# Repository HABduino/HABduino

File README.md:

## Habduino

This is the original code base for Habduino V4.X boards. It is still suitable for flights but is no longer maintained or supported. Hardware definitions are all current. 

This code provides simultaneous (where legal and supported by the hardware installed) transmission of radio telemetry via RTTY and APRS on Habduino Arduino addon boards for High Altitude Ballooning. 

## Move to Flextrack

We strongly recommend you move to Dave Akermans Flextrack as this is updated and maintained. We have forked the Flextrack code here https://github.com/HABduino/FlexTrack and made Habduino specific amendments.

## Disclaimer

The Habduino code is provided as is with no guarantees of performance or operation. 

If you decide to use this code under a balloon it’s your responsibility to ensure you comply with the local legislation and laws regarding meteorological balloon launching and radio transmission in the air. 
The Radiometrix NTX2B 434Mhz is NOT license exempt in the United States of America and does need a radio amateur license.

Use of APRS requires a radio amateur license in all countries and a number of countries don’t permit the airborne use of APRS under any circumstances. 

It is YOUR responsibility to ensure Habduino hardware and code is used safely and legally please review the safety section on the website. 

## Further Reading on High Altitude Ballooning

Please read this http://www.daveakerman.com/?p=1732

## License

The hardware design & code for Habduino is released under a Creative Commons License 3.0 Attribution-ShareAlike License : http://creativecommons.org/licenses/by-sa/3.0/

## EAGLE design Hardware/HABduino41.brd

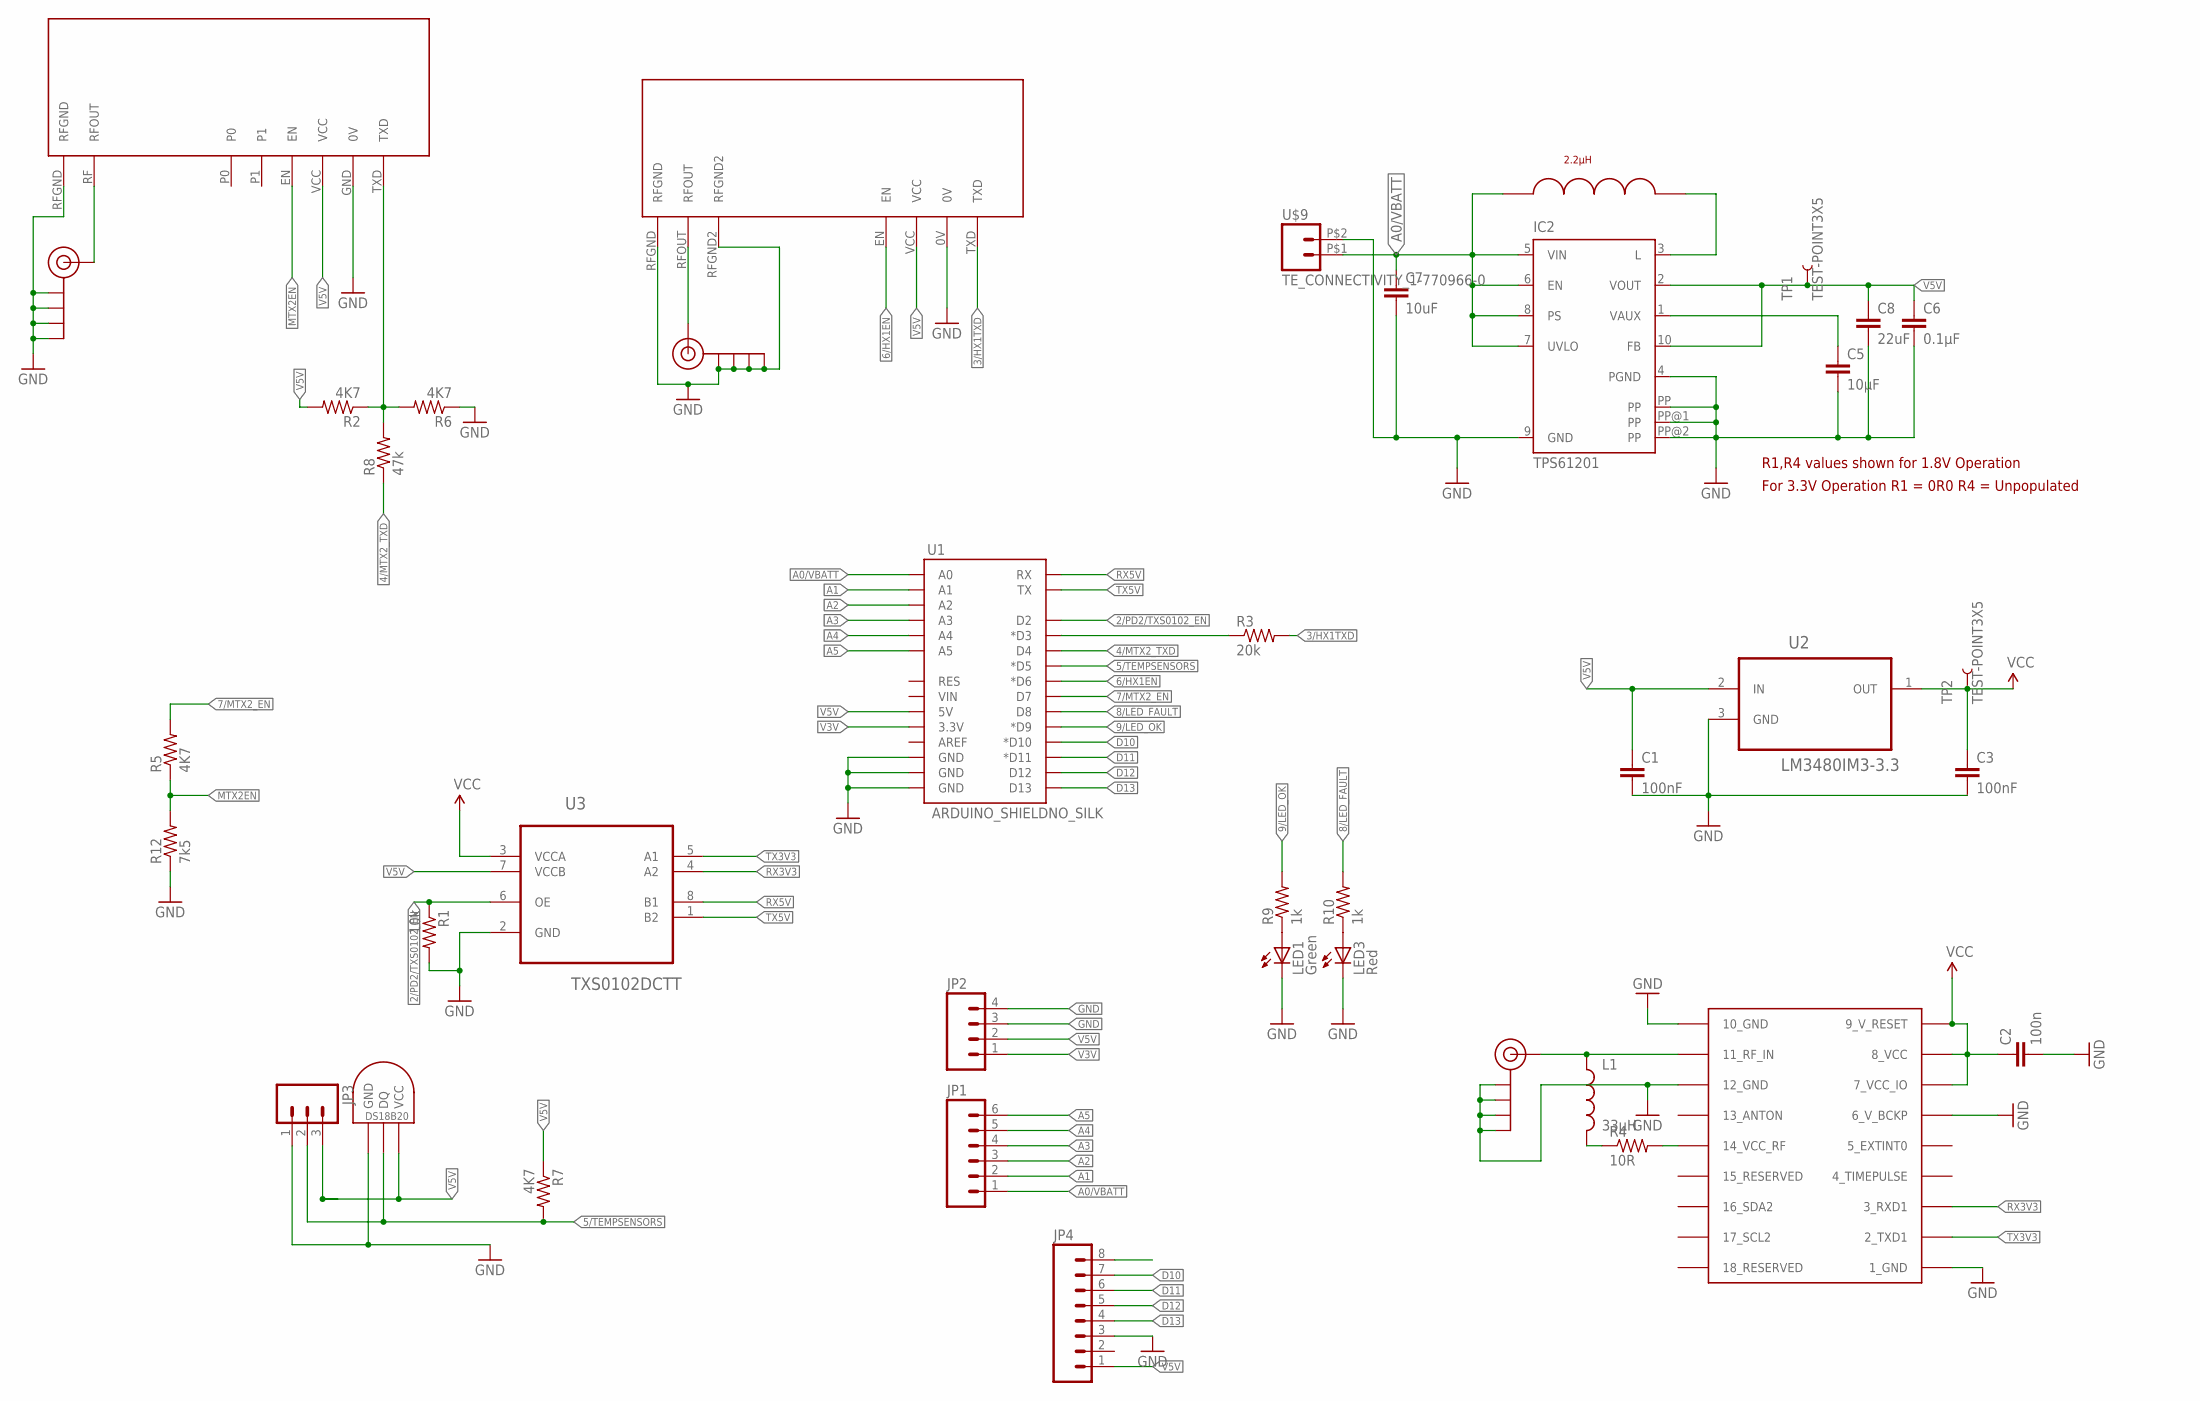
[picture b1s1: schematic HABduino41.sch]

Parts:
C1, C3: 100nF; 0603-CAP
C2: 100n; 0603-CAP
C5: 10µF; 0603-CAP
C6: 0.1µF; 0603-CAP
C7: 10uF; 1206
C8: 22uF; 1206
IC2: TPS61201; S-PDSO-N10
J$1, J$2, J$4: SMA_EDGE; SMA-EDGE
JP1: M06SIP; 1X06
JP2: M04PTH; 1X04
JP3: M03PTH; 1X03
JP4: M081X08; 1X08
L1: 33µH; 0603
LED1: Green; LED-0603
LED3: Red; LED-0603
LPS4018: 2.2µH; COILCRAFT_LPS4018
R1: 10k; 0603-RES
R2, R5, R6, R7: 4K7; 0603-RES
R3: 20k; 0603-RES
R4: 10R; 0603-RES
R8: 47k; 0603-RES
R9, R10: 1k; 0603-RES
R12: 7k5; 0603-RES
TEMP: DS1821; DS18B20_SOIC
TP1, TP2: TEST-POINT3X5; PAD.03X.05
U1: ARDUINO_SHIELDNO_SILK; DUEMILANOVE_VIAS
U2: LM3480IM3-3.3; SOT95P251X112-3N
U3: TXS0102DCTT; SOP65P400X130-8N
U$1: UBLOX_MAX
U$2: RADIOMETRIX-HX1
U$4: RADIOMETRIX-MTX2
U$9: TE_CONNECTIVITY_1-770966-0; FARNELL 1098556

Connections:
2/PD2/TXS0102_EN: R1.1, U1.D2, U3.6 (OE)
3/HX1TXD: R3.2, U$2.TXD
4/MTX2_TXD: R8.1, U1.D4
5/TEMPSENSORS: JP3.2, R7.2, TEMP.DQ, U1.D5 (*D5)
6/HX1EN: U1.D6 (*D6), U$2.EN
7/MTX2_EN: R5.2, U1.D7
8/LED_FAULT: R10.2, U1.D8
9/LED_OK: R9.2, U1.D9 (*D9)
A0/VBATT: C7.1, IC2.5 (VIN), IC2.6 (EN), IC2.7 (UVLO), IC2.8 (PS), JP1.1, LPS4018.P$1, U1.A0, U$9.P$1 (1)
A1: JP1.2, JP4.8, U1.A1
A2: JP1.3, U1.A2
A3: JP1.4, U1.A3
A4: JP1.5, U1.A4
A5: JP1.6, U1.A5
D10: JP4.7, U1.D10 (*D10)
D11: JP4.6, U1.D11 (*D11)
D12: JP4.5, U1.D12
D13: JP4.4, U1.D13
GND: C1.2, C2.2, C3.2, C5.2, C6.2, C7.2, C8.2, IC2.4 (PGND), IC2.9 (GND), IC2.PP, IC2.PP@1 (PP), IC2.PP@2 (PP), J$1.GND@0 (GND), J$1.GND@1 (GND), J$1.GND@2 (GND), J$1.GND@3 (GND), J$2.GND@0 (GND), J$2.GND@1 (GND), J$2.GND@2 (GND), J$2.GND@3 (GND), J$4.GND@0 (GND), J$4.GND@1 (GND), J$4.GND@2 (GND), J$4.GND@3 (GND), JP2.3, JP2.4, JP3.1, JP4.3, LED1.C, LED3.C, R1.2, R6.1, R12.1, TEMP.GND, U1.GND@0 (GND), U1.GND@1 (GND), U1.GND@2 (GND), U2.3 (GND), U3.2 (GND), U$1.1_GND, U$1.6_V_BCKP, U$1.10_GND, U$1.12_GND, U$2.0V, U$2.RFGND, U$2.RFGND2, U$4.GND (0V), U$4.RFGND, U$9.P$2 (2)
MTX2EN: R5.1, R12.2, U$4.EN
unnamed: R3.1, U1.D3 (*D3)
unnamed: J$1.SIG (SIGNAL), U$4.RF (RFOUT)
unnamed: J$2.SIG (SIGNAL), L1.1, U$1.11_RF_IN
unnamed: IC2.3 (L), LPS4018.P$2
unnamed: J$4.SIG (SIGNAL), U$2.RFOUT
unnamed: R2.1, R6.2, R8.2, U$4.TXD
unnamed: C5.1, IC2.1 (VAUX)
unnamed: LED1.A, R9.1
unnamed: LED3.A, R10.1
unnamed: L1.2, R4.1
unnamed: R4.2, U$1.14_VCC_RF
RX3V3: U3.4 (A2), U$1.3_RXD1
RX5V: U1.RX, U3.8 (B1)
TX3V3: U3.5 (A1), U$1.2_TXD1
TX5V: U1.TX, U3.1 (B2)
V3V: JP2.1, U1.3.3V
V5V: C1.1, C6.1, C8.1, IC2.2 (VOUT), IC2.10 (FB), JP2.2, JP3.3, JP4.1, R2.2, R7.1, TEMP.VCC, TP1.P$1, U1.5V, U2.2 (IN), U3.7 (VCCB), U$2.VCC, U$4.VCC
VCC: C2.1, C3.1, TP2.P$1, U2.1 (OUT), U3.3 (VCCA), U$1.7_VCC_IO, U$1.8_VCC, U$1.9_V_RESET

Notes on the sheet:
R1,R4 values shown for 1.8V Operation
For 3.3V Operation R1 = 0R0 R4 = Unpopulated

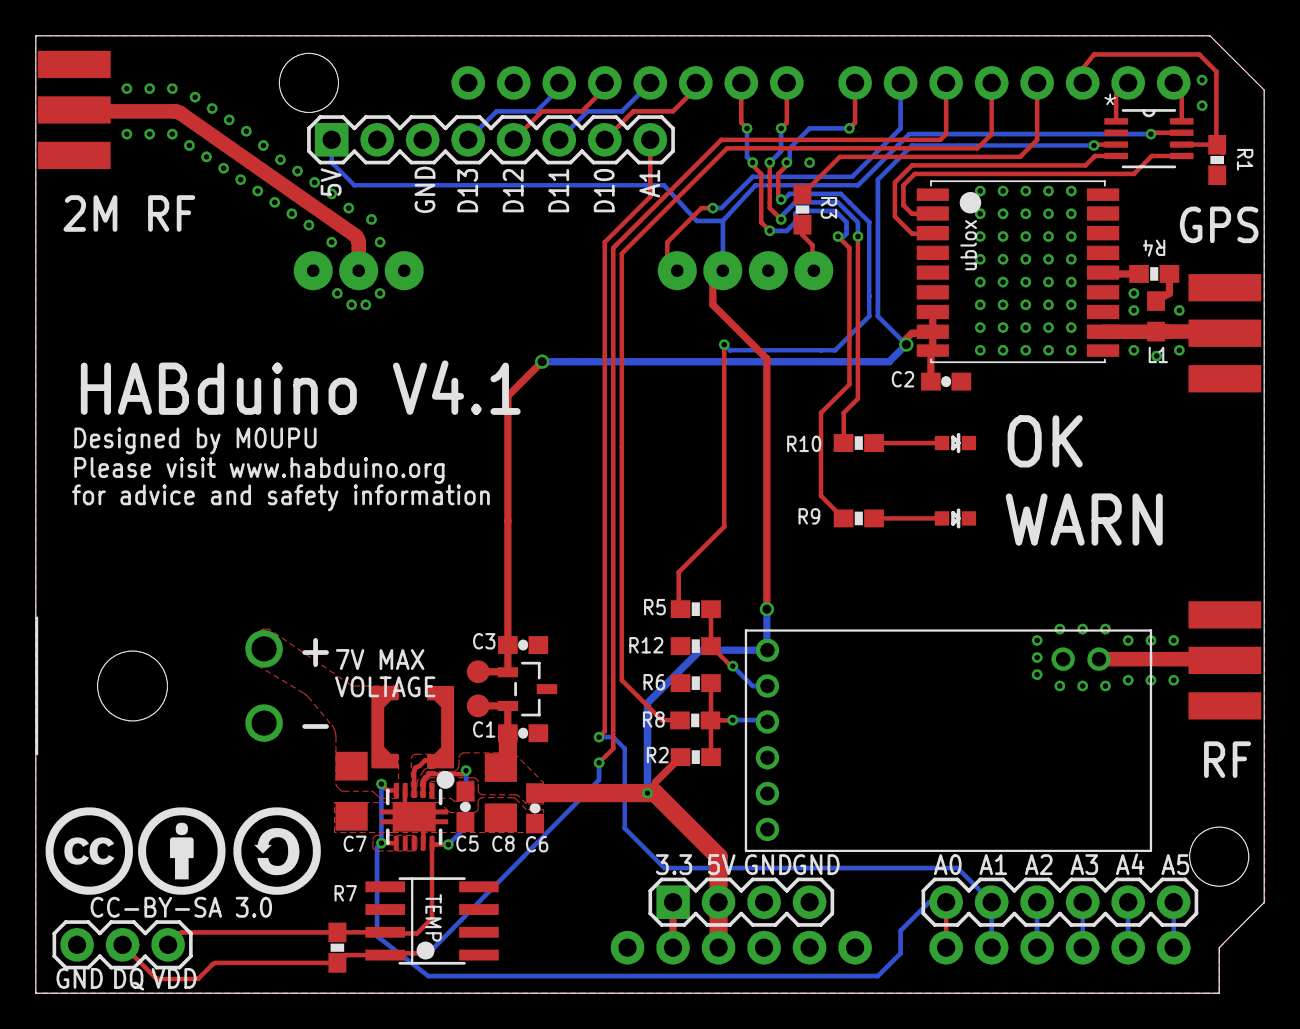
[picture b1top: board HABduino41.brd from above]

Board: 2 copper layers, 68.5 x 53.4 mm, 43 parts (1 on the bottom side), 38 nets.

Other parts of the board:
U$3: CC
U$5: CC-BY-21
U$6: CC-SA-21

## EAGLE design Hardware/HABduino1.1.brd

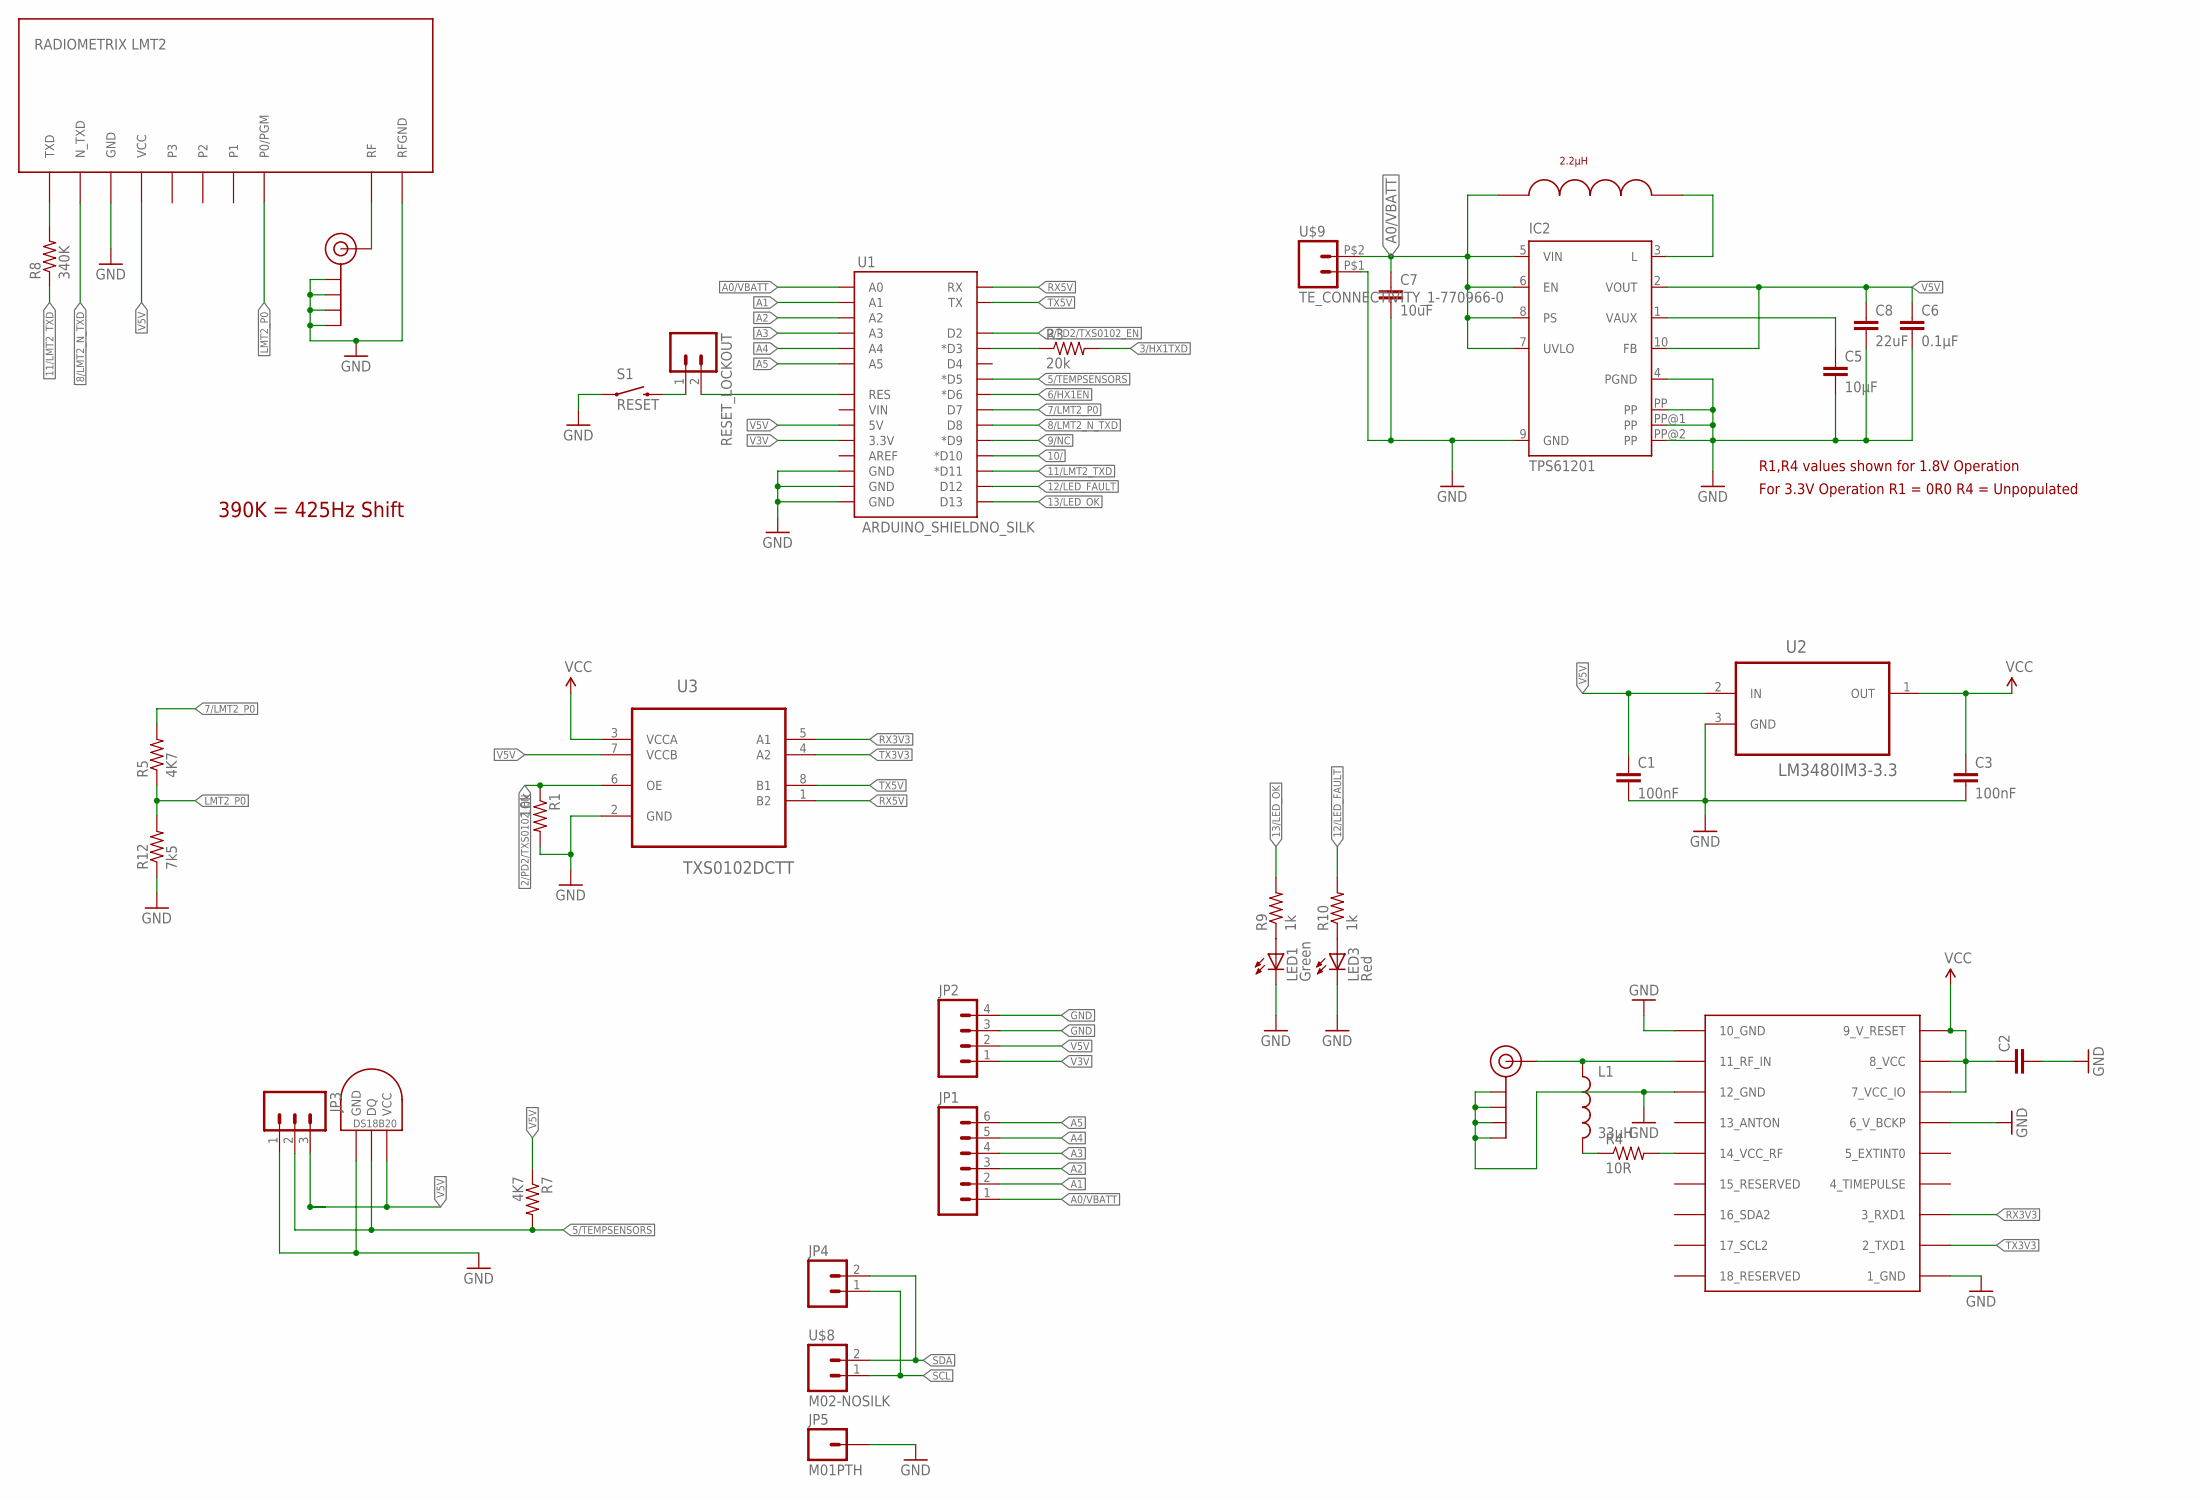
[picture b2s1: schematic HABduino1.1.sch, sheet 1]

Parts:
C1, C3: 100nF; 0603-CAP
C2: CAP0603-CAP; 0603-CAP
C5: 10µF; 0603-CAP
C6: 0.1µF; 0603-CAP
C7: 10uF; 1206
C8: 22uF; 1206
IC2: TPS61201; S-PDSO-N10
J$1, J$2: SMA_EDGE; SMA-EDGE
JP1: M06SIP; 1X06
JP2: M04PTH; 1X04
JP3: M03PTH; 1X03
JP4: M02PTH; 1X02
JP5: M01PTH; 1X01
L1: 33µH; 0603
LED1: Green; LED-0603
LED3: Red; LED-0603
R1: 10k; 0603-RES
R3: 20k; 0603-RES
R4: 10R; 0603-RES
R5, R7: 4K7; 0603-RES
R8: 340K; 0603-RES
R9, R10: 1k; 0603-RES
R12: 7k5; 0603-RES
RESET_LOCKOUT: M02PTH; 1X02
S1: RESET; TACTILE_SWITCH_TALL
TEMPINT: DS1821; DS1820
U1: ARDUINO_SHIELDNO_SILK; DUEMILANOVE_VIAS
U2: LM3480IM3-3.3; SOT95P251X112-3N
U3: TXS0102DCTT; SOP65P400X130-8N
U$1: UBLOX_MAX-6
U$2: RADIOMETRIX_LMT2; RADIOMETRIX-LMT2
U$8: M02-NOSILK
U$9: TE_CONNECTIVITY_1-770966-0; FARNELL 1098556
U$10: 2.2µH; COILCRAFT_LPS4018

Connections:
2/PD2/TXS0102_EN: R1.1, U1.D2, U3.6 (OE)
3/HX1TXD: R3.2; also elsewhere on the board
5/TEMPSENSORS: JP3.2, R7.2, TEMPINT.DQ, U1.D5 (*D5)
6/HX1EN: U1.D6 (*D6); also elsewhere on the board
7/LMT2_P0: R5.2, U1.D7
8/LMT2_N_TXD: U1.D8, U$2.N_TXE (N_TXD)
9/NC: U1.D9 (*D9)
10/: U1.D10 (*D10)
11/LMT2_TXD: R8.1, U1.D11 (*D11)
12/LED_FAULT: R10.2, U1.D12
13/LED_OK: R9.2, U1.D13
A0/VBATT: C7.1, IC2.5 (VIN), IC2.6 (EN), IC2.7 (UVLO), IC2.8 (PS), JP1.1, U1.A0, U$9.P$2 (2), U$10.P$1
A1: JP1.2, U1.A1
A2: JP1.3, U1.A2
A3: JP1.4, U1.A3
A4: JP1.5, U1.A4
A5: JP1.6, U1.A5
GND: C1.2, C2.2, C3.2, C5.2, C6.2, C7.2, C8.2, IC2.4 (PGND), IC2.9 (GND), IC2.PP, IC2.PP@1 (PP), IC2.PP@2 (PP), J$1.GND@0 (GND), J$1.GND@1 (GND), J$1.GND@2 (GND), J$1.GND@3 (GND), J$2.GND@0 (GND), J$2.GND@1 (GND), J$2.GND@2 (GND), J$2.GND@3 (GND), JP2.3, JP2.4, JP3.1, JP5.1, LED1.C, LED3.C, R1.2, R12.1, S1.A2 (1), TEMPINT.GND, U1.GND@0 (GND), U1.GND@1 (GND), U1.GND@2 (GND), U2.3 (GND), U3.2 (GND), U$1.1_GND, U$1.6_V_BCKP, U$1.10_GND, U$1.12_GND, U$2.GND, U$2.RFGND, U$9.P$1 (1); also elsewhere on the board
LMT2_P0: R5.1, R12.2, U$2.P0/PGM
unnamed: R3.1, U1.D3 (*D3)
unnamed: J$1.SIG (SIGNAL), U$2.RF
unnamed: J$2.SIG (SIGNAL), L1.1, U$1.11_RF_IN
unnamed: IC2.3 (L), U$10.P$2
unnamed: RESET_LOCKOUT.1, S1.B2 (2)
unnamed: RESET_LOCKOUT.2, U1.RES
unnamed: C5.1, IC2.1 (VAUX)
unnamed: LED1.A, R9.1
unnamed: LED3.A, R10.1
unnamed: L1.2, R4.1
unnamed: R4.2, U$1.14_VCC_RF
RX3V3: U3.5 (A1), U$1.3_RXD1
RX5V: U1.RX, U3.1 (B2)
SCL: JP4.1, U$8.1
SDA: JP4.2, U$8.2
TX3V3: U3.4 (A2), U$1.2_TXD1
TX5V: U1.TX, U3.8 (B1)
V3V: JP2.1, U1.3.3V
V5V: C1.1, C6.1, C8.1, IC2.2 (VOUT), IC2.10 (FB), JP2.2, JP3.3, R7.1, TEMPINT.VDD (VCC), U1.5V, U2.2 (IN), U3.7 (VCCB), U$2.VCC; also elsewhere on the board
VCC: C2.1, C3.1, U2.1 (OUT), U3.3 (VCCA), U$1.7_VCC_IO, U$1.8_VCC, U$1.9_V_RESET
_LMT2TXD: R8.2, U$2.TXD

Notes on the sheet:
390K = 425Hz Shift
R1,R4 values shown for 1.8V Operation
For 3.3V Operation R1 = 0R0 R4 = Unpopulated

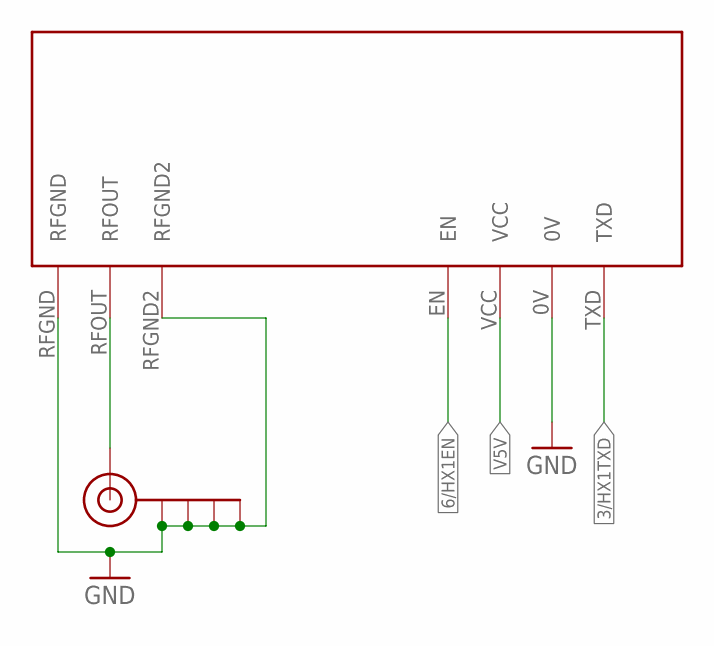
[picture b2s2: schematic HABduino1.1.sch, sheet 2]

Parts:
J$3: SMA_EDGE; SMA-EDGE
U$7: RADIOMETRIX-HX1

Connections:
3/HX1TXD: U$7.TXD; also elsewhere on the board
6/HX1EN: U$7.EN; also elsewhere on the board
GND: J$3.GND@0 (GND), J$3.GND@1 (GND), J$3.GND@2 (GND), J$3.GND@3 (GND), U$7.0V, U$7.RFGND, U$7.RFGND2; also elsewhere on the board
unnamed: J$3.SIG (SIGNAL), U$7.RFOUT
V5V: U$7.VCC; also elsewhere on the board

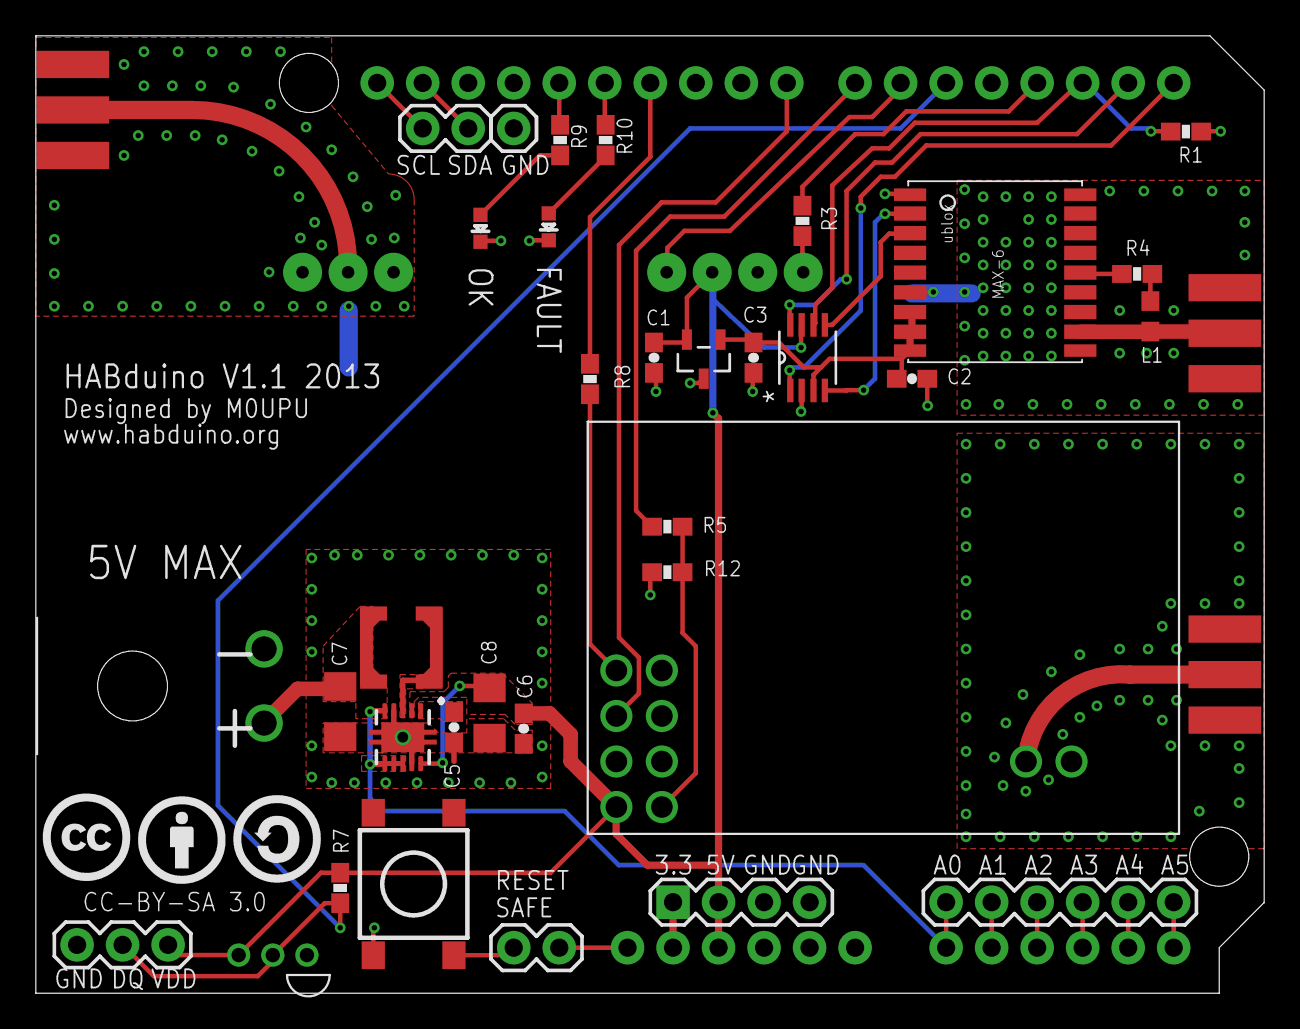
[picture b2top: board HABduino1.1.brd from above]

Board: 2 copper layers, 68.5 x 53.4 mm, 43 parts (1 on the bottom side), 39 nets.

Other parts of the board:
U$3: CC
U$5: CC-BY-21
U$6: CC-SA-21

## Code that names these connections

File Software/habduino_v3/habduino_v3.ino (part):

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#define TXDELAY 0        // Delay between sentence TX's
#define RTTY_BAUD 50     // RTTY Baud rate (Recommended = 50)
#define LED_WARN 12
#define LED_OK 13
#define BATTERY_ADC A0
#define MTX2_SHIFT 425        
#define MTX2_OFFSET 0          // 0-100 Slightly adjusts the frequency by increasing the PWM 
#define MTX2_TXD 11
#define MTX2_ENABLE 7


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uint8_t buf[60]; 
uint8_t lock =0, sats = 0, hour = 0, minute = 0, second = 0;
uint8_t oldhour = 0, oldminute = 0, oldsecond = 0;
int GPSerror = 0,navmode = 0,psm_status = 0,lat_int=0,lon_int=0,tempsensors,temperature1=0,temperature2=0;
int32_t lat = 0, lon = 0, alt = 0, maxalt = 0, lat_dec = 0, lon_dec =0 ,tslf=0;
unsigned long currentMillis;
long previousMillis = 0;
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

void setup()  { 
  pinMode(MTX2_TXD, OUTPUT);
  pinMode(LED_WARN, OUTPUT);
  pinMode(HX1_ENABLE, OUTPUT);
  pinMode(LED_OK,OUTPUT);
  pinMode(MTX2_ENABLE, OUTPUT);
  pinMode(GPS_ON, OUTPUT);
  pinMode(BATTERY_ADC, INPUT);
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
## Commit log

2013-06-27 Initial Commit
    Initial Commit of the Habduino code & Eagle files
2013-06-29 Updated BRD File + Added Sketchup Model
    1/ Removed GND via that linked VCC to GND (duh!)
    2/ Cleaned up silk screen.
    3/ Added location mark to TPS61200 module.
    4/ Added Sketchup Model
2013-07-02 Minor silk screen amendments
2013-07-18 Missing bstop & code mod
    Eagle board file was missing the bStop under the regulator making it
    very tricky to hand solder the TPS62100 module.
    Amended code in a number of places to remove aprs counter if not using
    APRS, switched warning LED's round.
2013-08-03 Updated error code description
    Put explanation of error codes in comments.
2013-08-12 Minor fix
    N_TXE was labelled N_TXD on the schematic. Fixed the net name.
2013-08-27 Added initial commit of the instruction manual
2013-09-01 Amended frequency selection
    Removed the per channel frequency selection and replace it with very
    granular frequency selection using Daniel Richmans LMT2 N&R Calculation
    code
2013-10-09 Revert "Amended frequency selection"
    This reverts commit e987e9935bc74b5b7e79517ef354fd362f5e6a4e.
2013-10-09 Revert "Revert "Amended frequency selection""
    This reverts commit e42edad16fc68c9f1d338c9440661a7b8e9a1fb2.
2013-11-06 Bug fixes and amended location
    Fixed a bug where the NMEA strings weren't turning off which caused the
    rest of the packets from the GPS to fail checksums.
    Moved to habduino subdirectory to please Arduino when downloading.
2013-11-06 Added code to stop garbage location data
    Ublox when running in UBX mode seem to give out garbage location data
    prior to getting a lock. This results in messy tracks all over
    spacenear.us.
    Added code to only give 0 lat,lon and alt if sats < 4.
2013-11-09 Fixed 2 bugs
    1/ https://github.com/HABduino/HABduino/issues/4
    2/ https://github.com/HABduino/HABduino/issues/5
2014-03-13 GPS Locking Bug
    Under certain circumstances GPS could lock up if antenna wasn't screwed
    on correctly and it had gone into PSM mode. Added code to put it back
    into max performance mode and eventually cold boot the GPS if having
    issues.
    Also added additional error bit 2 indicating an issue with temp sensor.
    Fixed warning LED blinking warning (now blinks at 1hz as expected when
2014-03-25 Additional Features added
    1/ Automatically detects a secondary temperature sensor and adds to
    telemetry
    2/ Reports battery voltage and smooths it.
    3/ Amended disclaimer/information.
2014-04-06 Fixed some spacing issues in code
    Closing brackets were off the edge of the screen.
2014-04-12 Amended telemetry string construction code
    Avoids potential bugs
2014-05-16 Amended txstring length
    https://github.com/HABduino/HABduino/issues/9
    Max length is 90 :
    $$ABCDEFGHI,65535,99:99:99,-123.123456,-123.123456,65535,99,-123,-123,65535,65535,FF*FFFF
    Made txstring 100 long
2014-05-17 Fixed RTTY Shift Bug when using APRS
    1/ Fixed RTTY shift bug when using APRS.
    2/ Removed setPwmFrequency routine entirely.
    3/ Moved the APRS settings into ax25modem.h
2014-07-28 Bug fix
    Variable was set too small
2014-07-28 Bug Fix
2014-09-02 Revert "Bug Fix"
    This reverts commit 4f761bcb3b1ebe6875d95b780ed67466d98a066d.
2014-09-02 Revert "Bug fix"
    This reverts commit 715a86ef62abbb9d4fb7681befcacc71bd26ad42.
2014-10-28 New hardware version 3.0
    Removed LMT2 and replaced with MTX2 transmitter.
    Removed TO92 DS18B20 and replaced with SMD version.
    Removed Reset Protect + Reset switch
    Switch power supply +/- round to match the Pi In The Sky.
    Minor Silk Screen amendments.
2014-11-04 Split scripts out into two versions
    V3 for the MTX2 based boards.
2014-11-04 Added Frequency Selection Code for MTX2
    Tuned shift setting for 425hz.
    Amended frequency selection code for MTX2
    Removed References to LMT2
2014-11-06 Added setGPS_GNSS
    MAX8's default to multi GNSS mode disabling power saving. Added code to
    disable all but GPS GNSS solutions. (Untested at this time)
2014-12-07 Cleaned up some unused code
2014-12-07 Removed unused code
    APRS Debugging
2014-12-07 Bug in APRS Fixed
    APRS wasn't decoding correctly. Massive thanks to Phil Heron for noting
    the Temp sensor was glitching the APRS transmission.
2015-03-30 Amended pins for Habduino V4 Hardware
2015-07-07 Update documentation
2015-12-09 Added V4.1 Hardware
    Added V4.1 Hardware
2017-07-14 Fixed call sign length bug
2017-07-17 I kan't spel
2017-07-17 Updated Readme's
2017-07-17 Updated documentation
2017-07-17 Amended readme

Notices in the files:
Software/habduino_v3/habduino_v3.ino:
This program is free software: you can redistribute it and/or modify
it under the terms of the GNU General Public License as published by
the Free Software Foundation, either version 3 of the License, or
(at your option) any later version.
See : http://creativecommons.org/licenses/by-sa/3.0
Hardware/HABduino1.1.brd:
CC-BY-SA 3.0
Released under the Creative Commons Attribution Share-Alike 3.0 License
